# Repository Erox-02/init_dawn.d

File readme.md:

# init_dawn.d

## comps

- Seeed Studio XIAO ESP32-C3
- 1x 2.25in TFT Screen
- 1x 3.3V Piezo Buzzer
- 5x MX-Style Keyboard Switches

## wiring

gnd(pin 1) -> gnd
---
vcc(pin 2) -> 3.3v out
---
scl(pin 3) -> D10
---
sda(pin 4) -> D8
---
rst(pin 5) -> D9
---
dc(pin 6) -> D7
---
cs(pin 7) -> D0
---
bl (pin 8) -> 3.3v out
---
SW1-sw5 1 pin on 3.3v and other pin on D1-D5 
---
Buzzer on D6 and gnd 
---

## feature

- Set alarm time (hour/minute)
- Multiple step sizes (1x, 2x, 5x, 10x, 12x)
- 5 alarm tones (Continuous, Beep, Fast, Siren, Melody)
- Snooze function
- Direction switching (up/down)

## controls

shift ->  change ladout (up/down)
---
hour  ->  adjust hours / snooze 
---
minute -> adjust minutes / snooze 
---
tone   -> change alarm tone / snooze 
---
multiplier -> change multipler / stop alarm 
---

## pcb

---

---

---

## cad

---

---

---

---

---

## License

MIT

## author

> Dipanjan Dutta
> I use arch btw

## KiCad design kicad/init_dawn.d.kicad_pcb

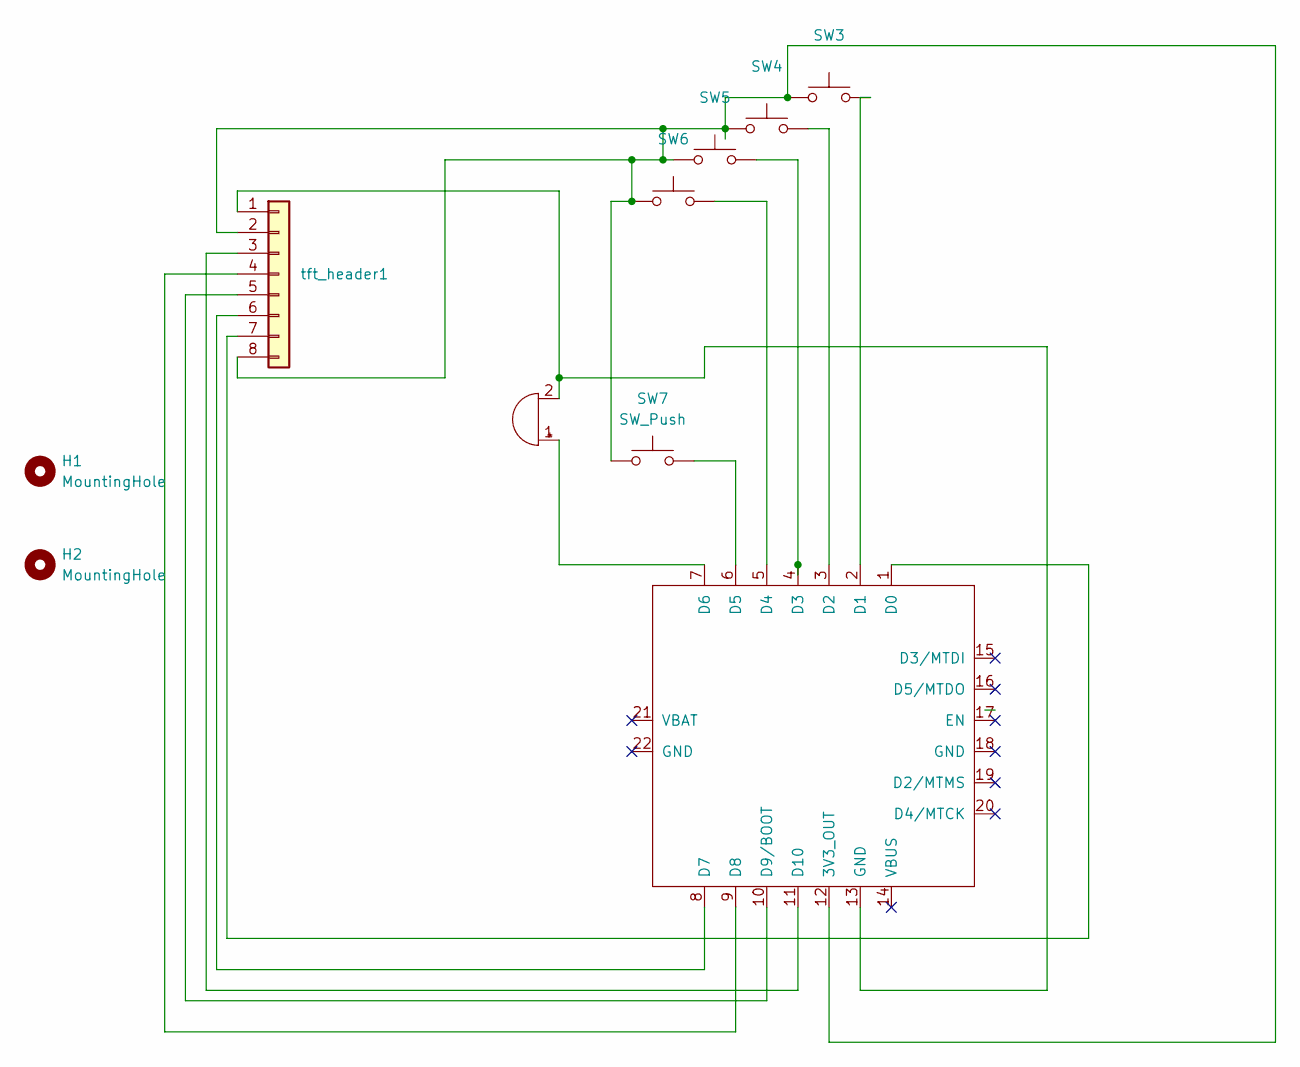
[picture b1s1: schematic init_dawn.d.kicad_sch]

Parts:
BZ1: Buzzer; Buzzer_12x9.5RM7.6
H1, H2: MountingHole; MountingHole_3.2mm_M3
SW3, SW5: SW_Cherry_MX_1.00u_PCB
SW4, SW6, SW7: SW_Push; SW_Cherry_MX_1.00u_PCB
U2: XIAO-ESP32-C3-SMD
tft_header1: Conn_01x08; PinHeader_1x08_P2.54mm_Vertical

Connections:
unnamed: BZ1.1 (+), U2.7 (D6)
unnamed: BZ1.2 (-), U2.13 (GND), tft_header1.1
unnamed: SW3.1, SW4.1, SW5.1, SW6.1, SW7.1, U2.12 (3V3_OUT), tft_header1.2, tft_header1.8
unnamed: U2.1 (D0), tft_header1.7
unnamed: SW3.2, U2.2 (D1)
unnamed: SW4.2, U2.3 (D2)
unnamed: SW5.2, U2.4 (D3)
unnamed: SW6.2, U2.5 (D4)
unnamed: SW7.2, U2.6 (D5)
unnamed: U2.8 (D7), tft_header1.6
unnamed: U2.9 (D8), tft_header1.4
unnamed: U2.10 (D9/BOOT), tft_header1.5
unnamed: U2.11 (D10), tft_header1.3

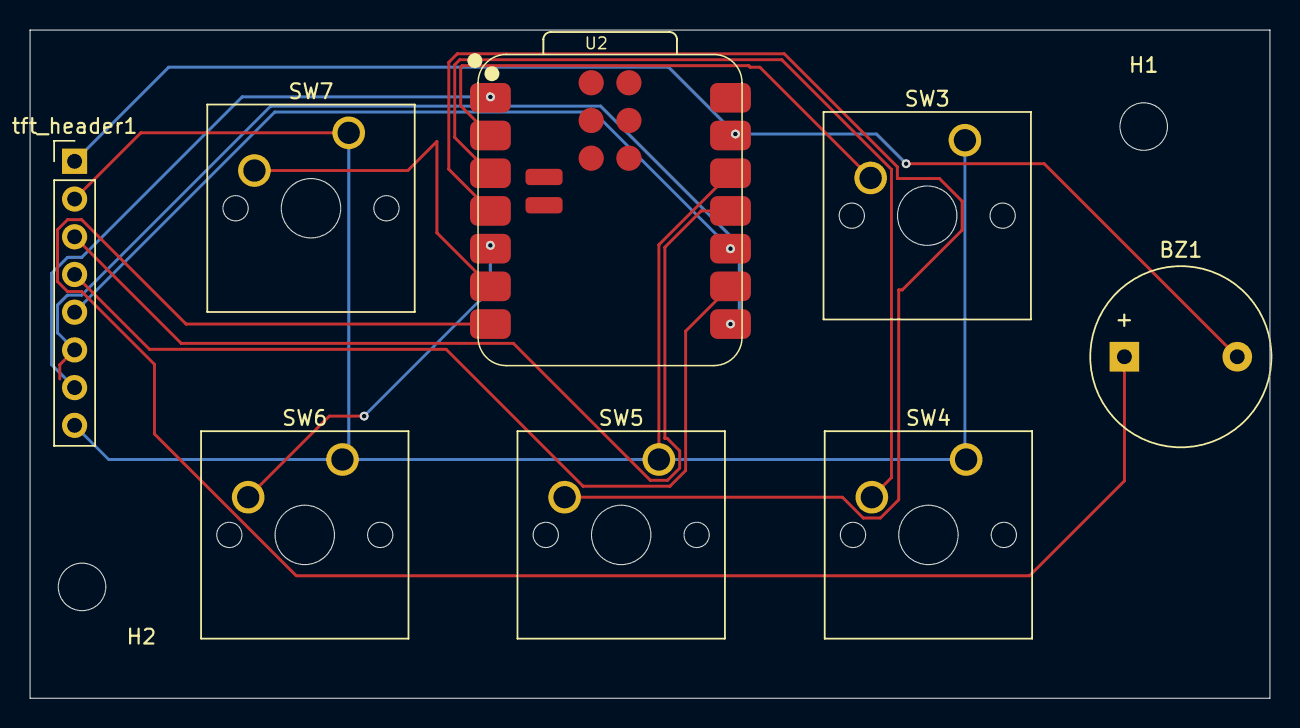
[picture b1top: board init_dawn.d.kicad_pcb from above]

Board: 2 copper layers, 83.5 x 45.0 mm, 10 parts (0 on the bottom side), 13 nets.
